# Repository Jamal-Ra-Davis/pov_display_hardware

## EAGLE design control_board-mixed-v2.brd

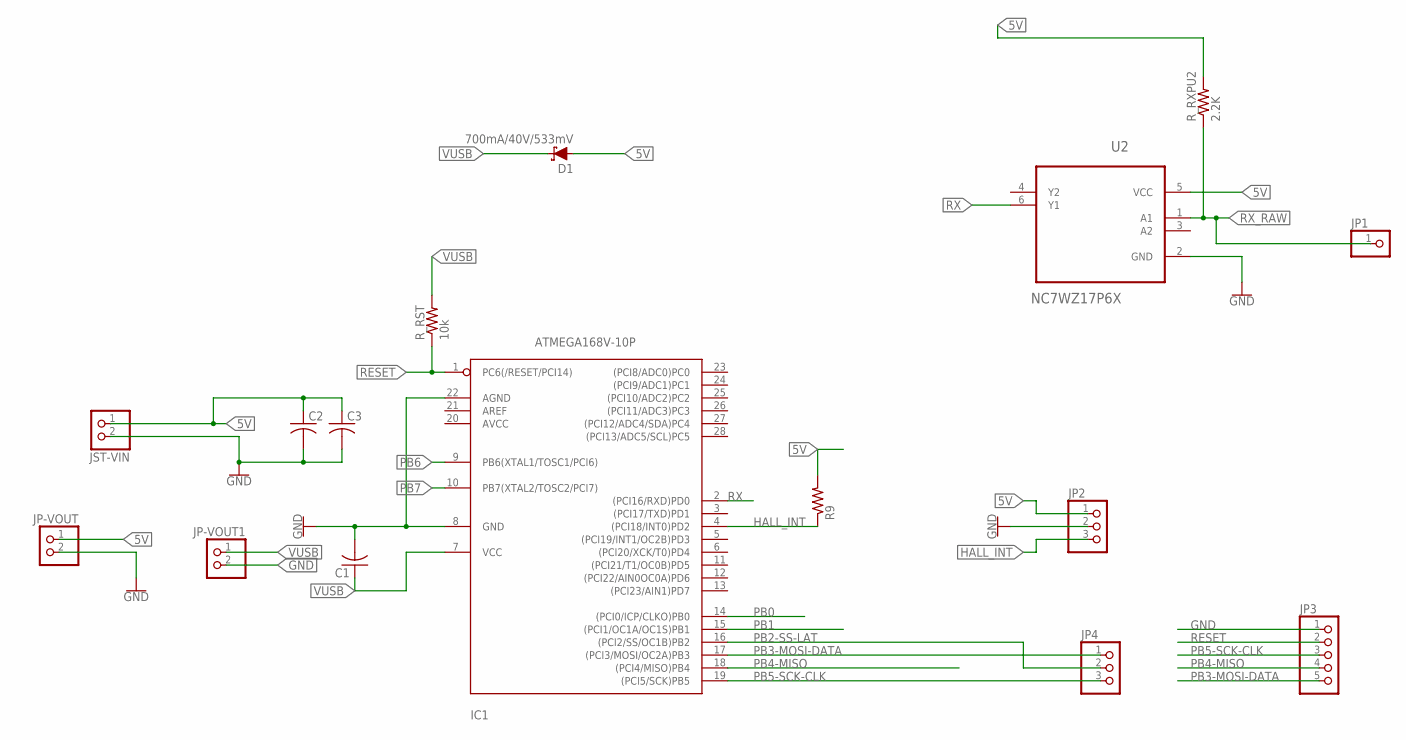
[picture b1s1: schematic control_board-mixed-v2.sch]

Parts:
C1: C-US025-030X050; C025-030X050
C2, C3: C-US025-060X050; C025-060X050
D1: 700mA/40V/533mV; SOT23-3
IC1: ATMEGA168V-10P; DIL28-3
JP1: PINHD-1X1; 1X01
JP2, JP4: PINHD-1X3; 1X03
JP3: PINHD-1X5; 1X05
JP-VOUT, JP-VOUT1: PINHD-1X2; 1X02
JST-VIN: JST_2PIN-THM-RA; JST-PH-2-THM-RA
R9: R-US_0207/7; 0207/7
R_RST: 10k; R0603
R_RXPU2: 2.2K; R0603
U2: NC7WZ17P6X; SOT65P210X110-6N

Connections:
5V: C2.1, C3.1, D1.1 (A), JP2.1, JP-VOUT.1, JST-VIN.1 (2), R9.2, R_RXPU2.2, U2.5 (VCC)
GND: C1.2, C2.2, C3.2, IC1.8 (GND), IC1.22 (AGND), JP2.2, JP3.1, JP-VOUT.2, JP-VOUT1.2, JST-VIN.2 (1), U2.2 (GND)
HALL_INT: IC1.4 ((PCI18/INT0)PD2), JP2.3, R9.1
PB0: IC1.14 ((PCI0/ICP/CLKO)PB0)
PB1: IC1.15 ((PCI1/OC1A/OC1S)PB1)
PB2-SS-LAT: IC1.16 ((PCI2/SS/OC1B)PB2), JP4.2
PB3-MOSI-DATA: IC1.17 ((PCI3/MOSI/OC2A)PB3), JP3.5, JP4.1
PB4-MISO: IC1.18 ((PCI4/MISO)PB4), JP3.4
PB5-SCK-CLK: IC1.19 ((PCI5/SCK)PB5), JP3.3, JP4.3
PB6: IC1.9 (PB6(XTAL1/TOSC1/PCI6))
PB7: IC1.10 (PB7(XTAL2/TOSC2/PCI7))
RESET: IC1.1 (PC6(/RESET/PCI14)), JP3.2, R_RST.1
RX: IC1.2 ((PCI16/RXD)PD0), U2.6 (Y1)
RX_RAW: JP1.1, R_RXPU2.1, U2.1 (A1)
VUSB: C1.1, D1.3 (C), IC1.7 (VCC), JP-VOUT1.1, R_RST.2

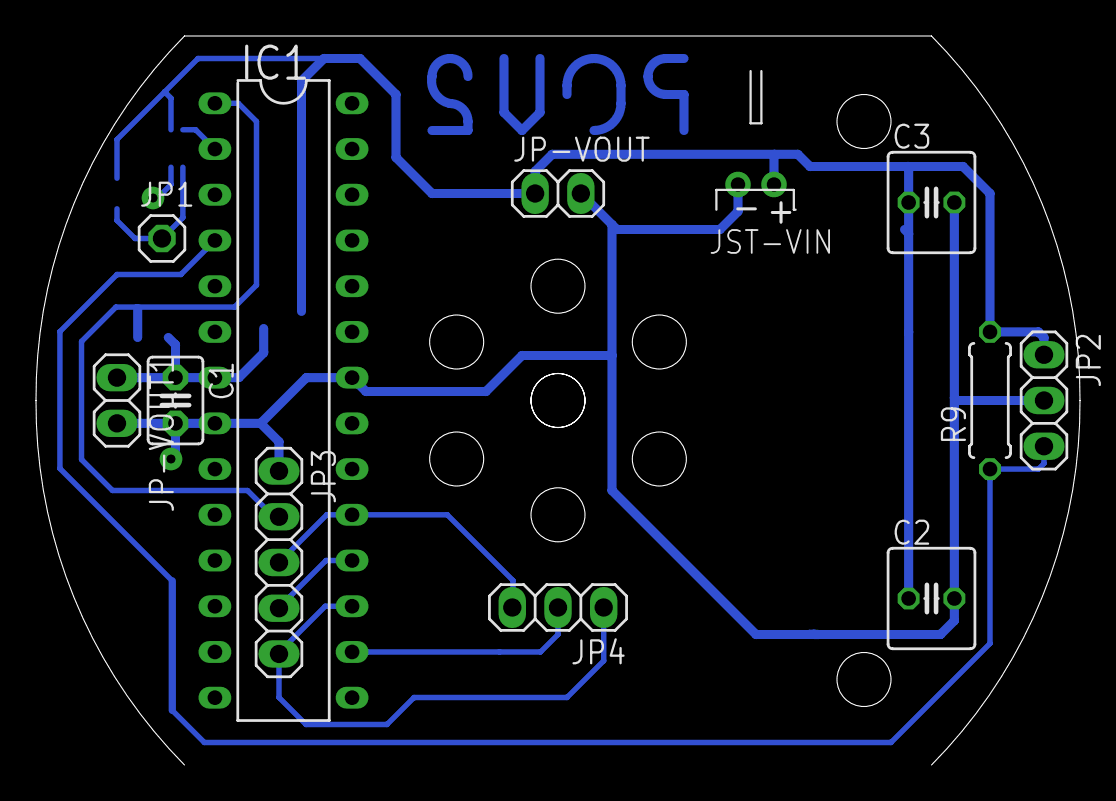
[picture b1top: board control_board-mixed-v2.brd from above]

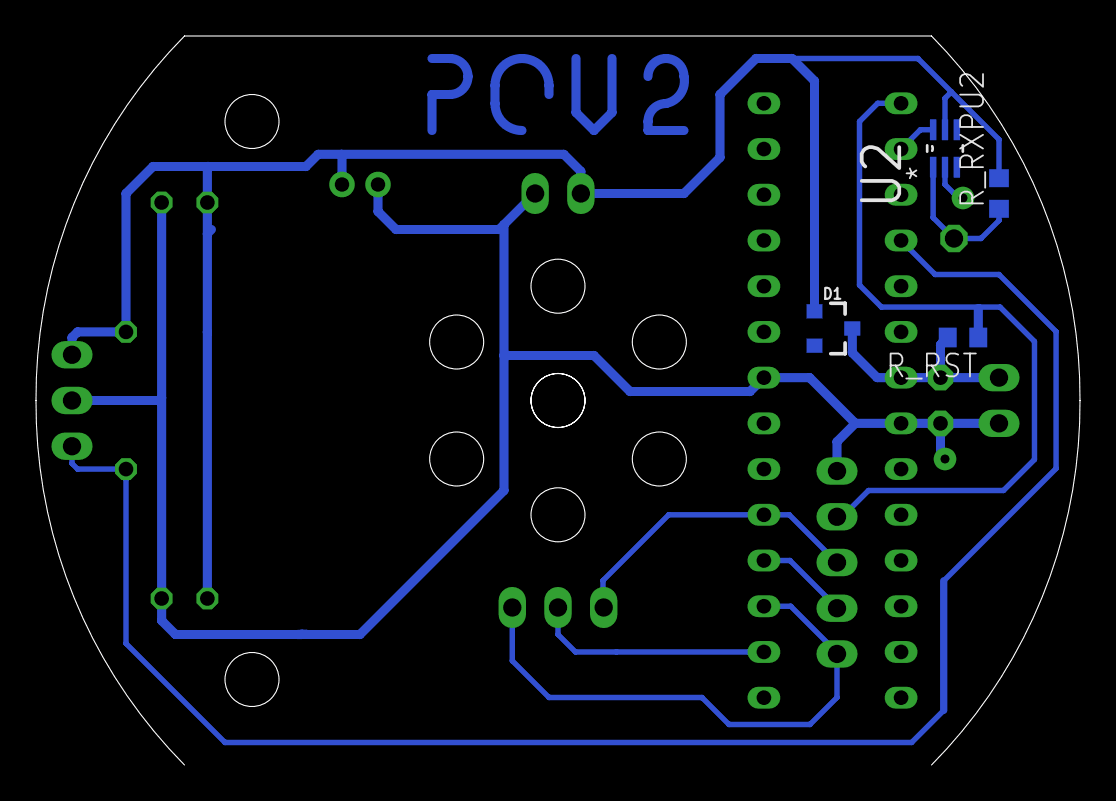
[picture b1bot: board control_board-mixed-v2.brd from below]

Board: 2 copper layers, 58.0 x 40.5 mm, 16 parts (4 on the bottom side), 11 nets.

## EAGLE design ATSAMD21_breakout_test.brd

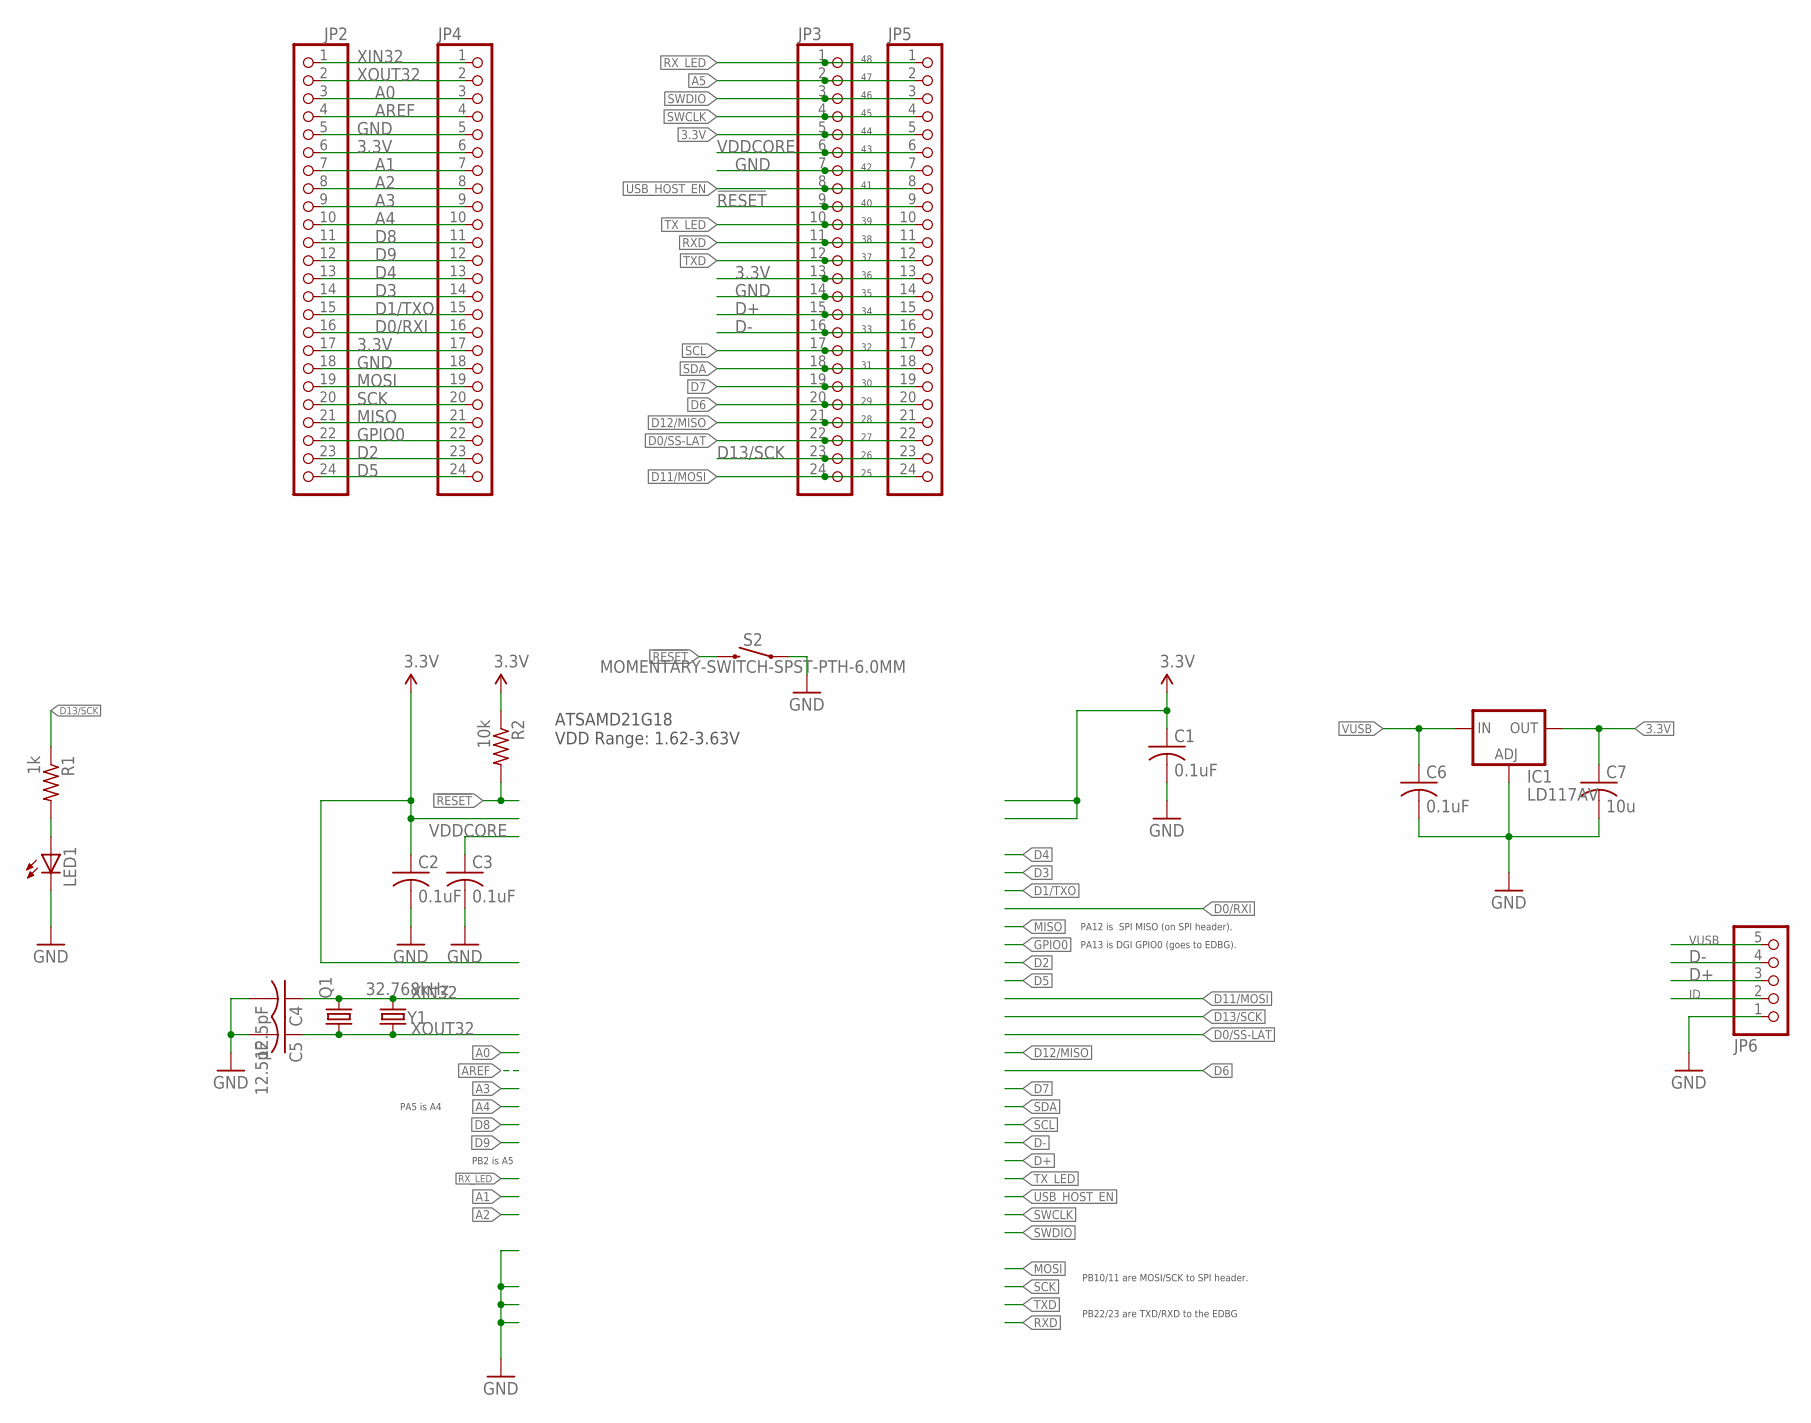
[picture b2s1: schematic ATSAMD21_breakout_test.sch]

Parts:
C1, C2, C3, C6: 0.1uF; C025-024X044
C4, C5: 12.5pF; C025-024X044
C7: 10u; C025-024X044
IC1: LD117AV; TO220L1
JP2, JP3, JP4, JP5: PINHD-1X24; 1X24
JP6: PINHD-1X5; 1X05
LED1: LED3MM
Q1: CRYSTALTC26V; TC26V
R1: 1k; 0204/7
R2: 10k; 0204/7
S2: MOMENTARY-SWITCH-SPST-PTH-6.0MM; TACTILE_SWITCH_PTH_6.0MM
Y1: 32.768kHz; CRYSTAL-SMD-3.2X1.5MM

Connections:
3.3V: C1.1, C2.1, C7.1, IC1.2 (OUT), JP2.6, JP2.17, JP3.5, JP3.13, JP4.6, JP4.17, JP5.5, JP5.13, R2.1
!RESET: JP3.9, JP5.9, R2.2, S2.3 (2)
A0: JP2.3, JP4.3
A1: JP2.7, JP4.7
A2: JP2.8, JP4.8
A3: JP2.9, JP4.9
A4: JP2.10, JP4.10
A5: JP3.2, JP5.2
AREF: JP2.4, JP4.4
D0/RXI: JP2.16, JP4.16
D0/SS-LAT: JP3.22, JP5.22
D1/TXO: JP2.15, JP4.15
D2: JP2.23, JP4.23
D3: JP2.14, JP4.14
D4: JP2.13, JP4.13
D5: JP2.24, JP4.24
D6: JP3.20, JP5.20
D7: JP3.19, JP5.19
D8: JP2.11, JP4.11
D9: JP2.12, JP4.12
D11/MOSI: JP3.24, JP5.24
D12/MISO: JP3.21, JP5.21
D13/SCK: JP3.23, JP5.23, R1.1
D+: JP3.15, JP5.15, JP6.3
D-: JP3.16, JP5.16, JP6.4
GND: C1.2, C2.2, C3.2, C4.2, C5.2, C6.2, C7.2, IC1.1 (ADJ), JP2.5, JP2.18, JP3.7, JP3.14, JP4.5, JP4.18, JP5.7, JP5.14, JP6.1, LED1.K (C), S2.1
GPIO0: JP2.22, JP4.22
ID: JP6.2
MISO: JP2.21, JP4.21
MOSI: JP2.19, JP4.19
unnamed: LED1.A, R1.2
RXD: JP3.11, JP5.11
RX_LED: JP3.1, JP5.1
SCK: JP2.20, JP4.20
SCL: JP3.17, JP5.17
SDA: JP3.18, JP5.18
SWCLK: JP3.4, JP5.4
SWDIO: JP3.3, JP5.3
TXD: JP3.12, JP5.12
TX_LED: JP3.10, JP5.10
USB_HOST_EN: JP3.8, JP5.8
VDDCORE: C3.1, JP3.6, JP5.6
VUSB: C6.1, IC1.3 (IN), JP6.5
XIN32: C4.1, JP2.1, JP4.1, Q1.2, Y1.P$2 (2)
XOUT32: C5.1, JP2.2, JP4.2, Q1.1, Y1.P$1 (1)

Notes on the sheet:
PB22/23 are TXD/RXD to the EDBG
PB10/11 are MOSI/SCK to SPI header.
PA12 is SPI MISO (on SPI header).
PA13 is DGI GPIO0 (goes to EDBG).
PA5 is A4
PB2 is A5
ATSAMD21G18 VDD Range: 1.62-3.63V

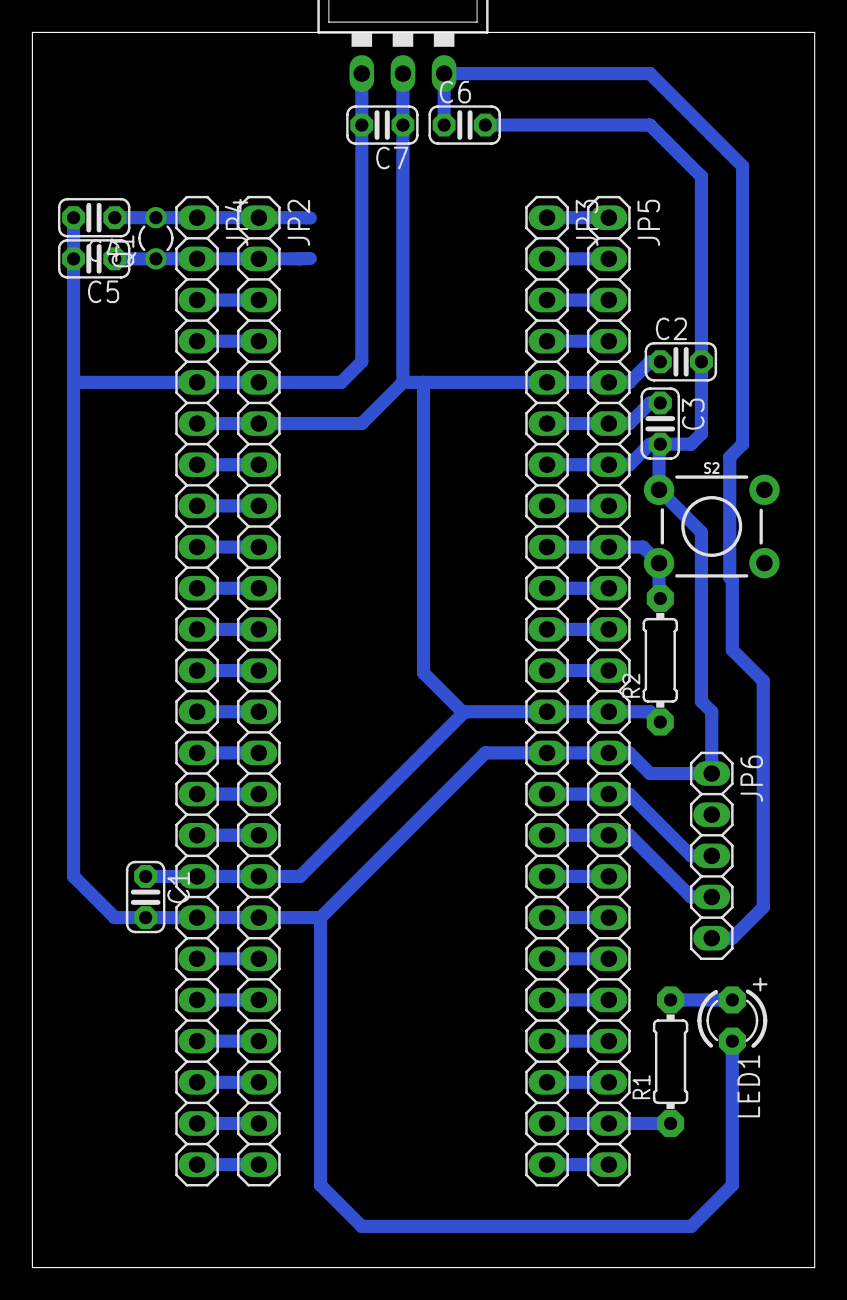
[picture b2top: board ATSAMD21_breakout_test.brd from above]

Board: 2 copper layers, 48.3 x 76.2 mm, 19 parts (1 on the bottom side), 44 nets.

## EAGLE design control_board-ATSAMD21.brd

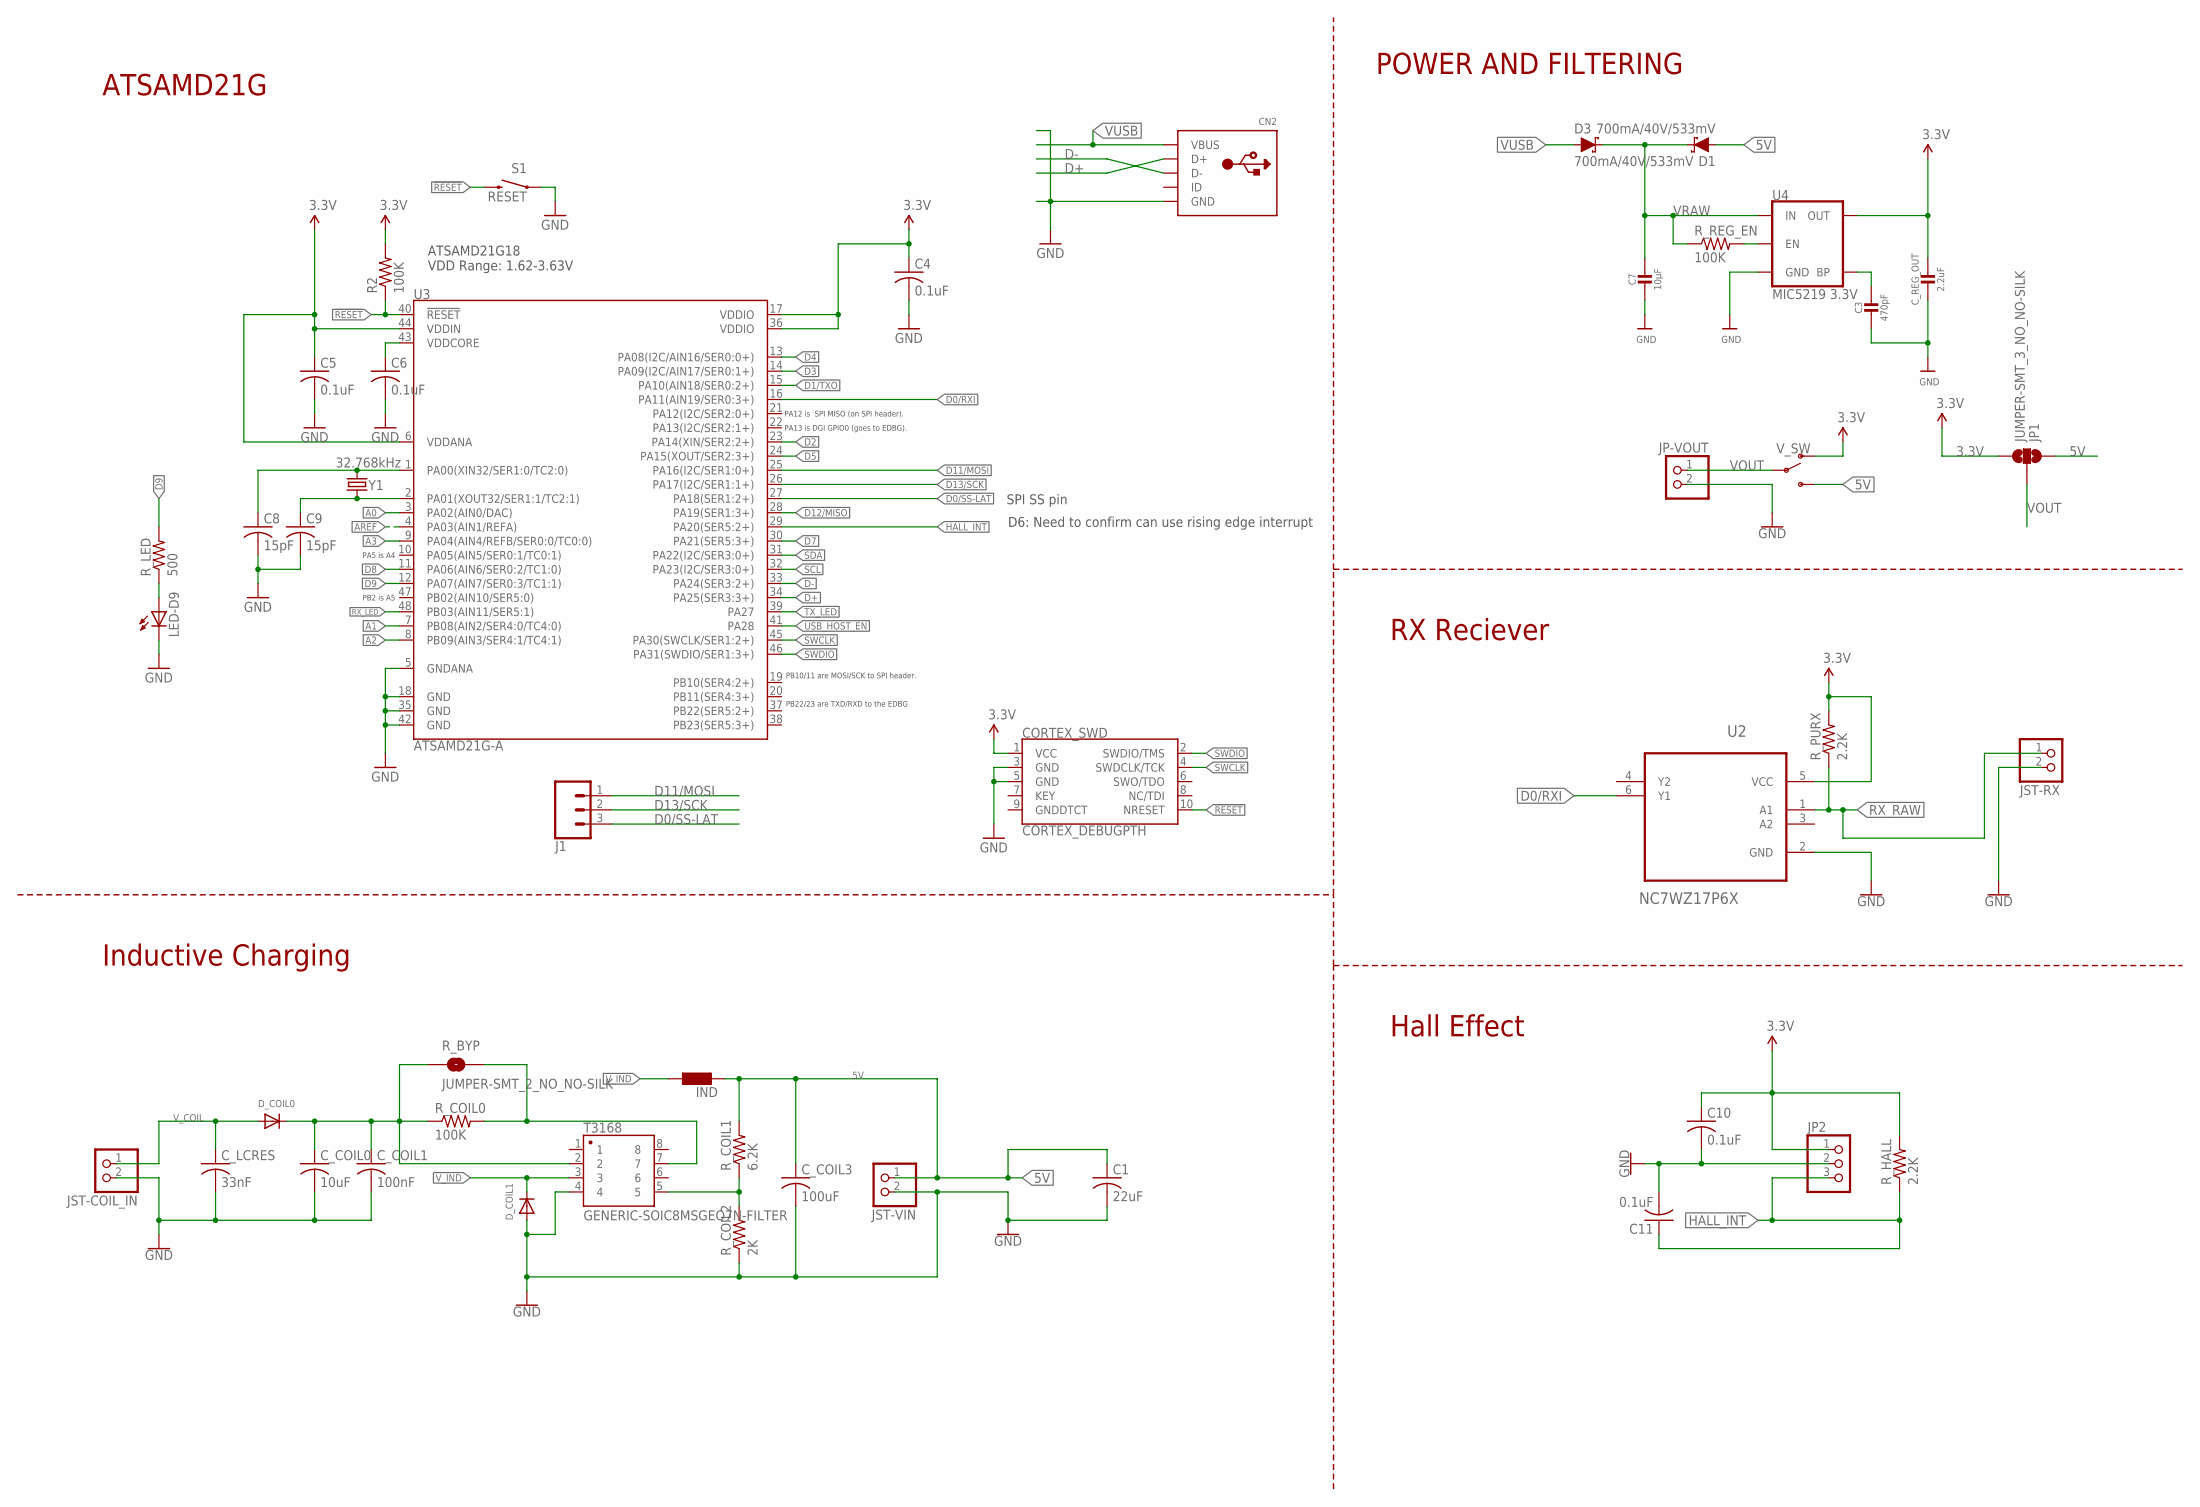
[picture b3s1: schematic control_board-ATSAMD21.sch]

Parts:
C1: 22uF; C1206
C3: 470pF; 0603-NO
C4, C5, C6, C10, C11: 0.1uF; C0603
C7: 10µF; 0805-NO
C8, C9: 15pF; C0603
CN2: USBTHM; USB-MINIB-THM
CORTEX_SWD: CORTEX_DEBUGPTH; 2X5-PTH-1.27MM
C_COIL0: 10uF; C1206
C_COIL1: 100nF; C1206
C_COIL3: 100uF; C1206
C_LCRES: 33nF; C1206
C_REG_OUT: 2.2uF; 0805-NO
D1, D3: 700mA/40V/533mV; SOT23-3
D_COIL0: DIODESMA; SMADIODE
D_COIL1: DIODE_SOD-123FL; SOD-123FL
IND: LL3230M; L3230M
J1: CONN_031X03_NO_SILK; 1X03_NO_SILK
JP1: JUMPER-SMT_3_NO_NO-SILK; SMT-JUMPER_3_NO_NO-SILK
JP2: PINHD-1X3; 1X03
JP-VOUT: PINHD-1X2; 1X02
JST-COIL_IN: JST_2PIN-THM-RA; JST-PH-2-THM-RA
JST-RX: JST_2PIN-THM-RA; JST-PH-2-THM-RA
JST-VIN: JST_2PIN-THM-RA; JST-PH-2-THM-RA
LED-D9: LEDCHIPLED_0603; CHIPLED_0603
R2: 100K; 0603-RES
R_BYP: JUMPER-SMT_2_NO_NO-SILK; SMT-JUMPER_2_NO_NO-SILK
R_COIL0: 100K; R0603
R_COIL1: 6.2K; R0603
R_COIL2: 2K; R0603
R_HALL: 2.2K; R0805
R_LED: 500; R0603
R_PURX: 2.2K; R0603
R_REG_EN: 100K; R0603
S1: RESET; TACTILE_SWITCH_SMD_4.6X2.8MM
T3168: GENERIC-SOIC8MSGEQ7N-FILTER; SO08
U2: NC7WZ17P6X; SOT65P210X110-6N
U3: ATSAMD21G-A; TQFP-48
U4: MIC5219 3.3V; SOT23-5
V_SW: SWITCH-SPDT-SMD-RIGHT-ANGLE; SWITCH_SPST_SMD_A
Y1: 32.768kHz; CRYSTAL-SMD-3.2X1.5MM

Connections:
3.3V: C4.1, C5.1, C10.1, CORTEX_SWD.1 (VCC), C_REG_OUT.1, JP1.3, JP2.1, R2.2, R_HALL.2, R_PURX.2, U2.5 (VCC), U3.6 (VDDANA), U3.17 (VDDIO), U3.36 (VDDIO), U3.44 (VDDIN), U4.5 (OUT), V_SW.1 (O)
5V: C1.1, C_COIL3.1, D1.1 (A), IND.2, JP1.1, JST-VIN.1 (2), R_COIL1.2, V_SW.3 (S)
!RESET: CORTEX_SWD.10 (NRESET), R2.1, S1.3 (2), S1.4 (2), U3.40 (!RESET!)
A0: U3.3 (PA02(AIN0/DAC))
A1: U3.7 (PB08(AIN2/SER4:0/TC4:0))
A2: U3.8 (PB09(AIN3/SER4:1/TC4:1))
A3: U3.9 (PA04(AIN4/REFB/SER0:0/TC0:0))
AREF: U3.4 (PA03(AIN1/REFA))
D0/RXI: U2.6 (Y1), U3.16 (PA11(AIN19/SER0:3+))
D0/SS-LAT: J1.3, U3.27 (PA18(SER1:2+))
D1/TXO: U3.15 (PA10(AIN18/SER0:2+))
D2: U3.23 (PA14(XIN/SER2:2+))
D3: U3.14 (PA09(I2C/AIN17/SER0:1+))
D4: U3.13 (PA08(I2C/AIN16/SER0:0+))
D5: U3.24 (PA15(XOUT/SER2:3+))
D7: U3.30 (PA21(SER5:3+))
D8: U3.11 (PA06(AIN6/SER0:2/TC1:0))
D9: R_LED.2, U3.12 (PA07(AIN7/SER0:3/TC1:1))
D11/MOSI: J1.1, U3.25 (PA16(I2C/SER1:0+))
D12/MISO: U3.28 (PA19(SER1:3+))
D13/SCK: J1.2, U3.26 (PA17(I2C/SER1:1+))
D+: CN2.D+, U3.34 (PA25(SER3:3+))
D-: CN2.D-, U3.33 (PA24(SER3:2+))
GND: C1.2, C3.2, C4.2, C5.2, C6.2, C7.2, C8.2, C9.2, C10.2, C11.2, CN2.GND, CORTEX_SWD.3 (GND), CORTEX_SWD.5 (GND), C_COIL0.2, C_COIL1.2, C_COIL3.2, C_LCRES.2, C_REG_OUT.2, D_COIL1.A, JP2.2, JP-VOUT.2, JST-COIL_IN.2 (1), JST-RX.2 (1), JST-VIN.2 (1), LED-D9.C, R_COIL2.1, S1.1, S1.2 (1), T3168.4, U2.2 (GND), U3.5 (GNDANA), U3.18 (GND), U3.35 (GND), U3.42 (GND), U4.2 (GND)
HALL_INT: C11.1, JP2.3, R_HALL.1, U3.29 (PA20(SER5:2+))
unnamed: C_COIL0.1, C_COIL1.1, D_COIL0.C, R_BYP.1, R_COIL0.1, T3168.2
unnamed: C8.1, U3.1 (PA00(XIN32/SER1:0/TC2:0)), Y1.P$2 (2)
unnamed: R_COIL1.1, R_COIL2.2, T3168.5
unnamed: C9.1, U3.2 (PA01(XOUT32/SER1:1/TC2:1)), Y1.P$1 (1)
unnamed: R_REG_EN.2, U4.3 (EN)
unnamed: C3.1, U4.4 (BP)
unnamed: R_BYP.2, R_COIL0.2, T3168.7
unnamed: LED-D9.A, R_LED.1
RX_LED: U3.48 (PB03(AIN11/SER5:1))
RX_RAW: JST-RX.1 (2), R_PURX.1, U2.1 (A1)
SCL: U3.32 (PA23(I2C/SER3:0+))
SDA: U3.31 (PA22(I2C/SER3:0+))
SWCLK: CORTEX_SWD.4 (SWDCLK/TCK), U3.45 (PA30(SWCLK/SER1:2+))
SWDIO: CORTEX_SWD.2 (SWDIO/TMS), U3.46 (PA31(SWDIO/SER1:3+))
TX_LED: U3.39 (PA27)
USB_HOST_EN: U3.41 (PA28)
VDDCORE: C6.1, U3.43 (VDDCORE)
VOUT: JP1.2, JP-VOUT.1, V_SW.2
VRAW: C7.1, D1.3 (C), D3.3 (C), R_REG_EN.1, U4.1 (IN)
VUSB: CN2.VBUS, D3.1 (A)
V_COIL: C_LCRES.1, D_COIL0.A, JST-COIL_IN.1 (2)
V_IND: D_COIL1.C, IND.1, T3168.3

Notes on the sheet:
POWER AND FILTERING
PB22/23 are TXD/RXD to the EDBG
PB10/11 are MOSI/SCK to SPI header.
PA12 is SPI MISO (on SPI header).
PA13 is DGI GPIO0 (goes to EDBG).
PA5 is A4
PB2 is A5
ATSAMD21G
ATSAMD21G18 VDD Range: 1.62-3.63V
SPI SS pin
D6: Need to confirm can use rising edge interrupt
Inductive Charging
RX Reciever
Hall Effect

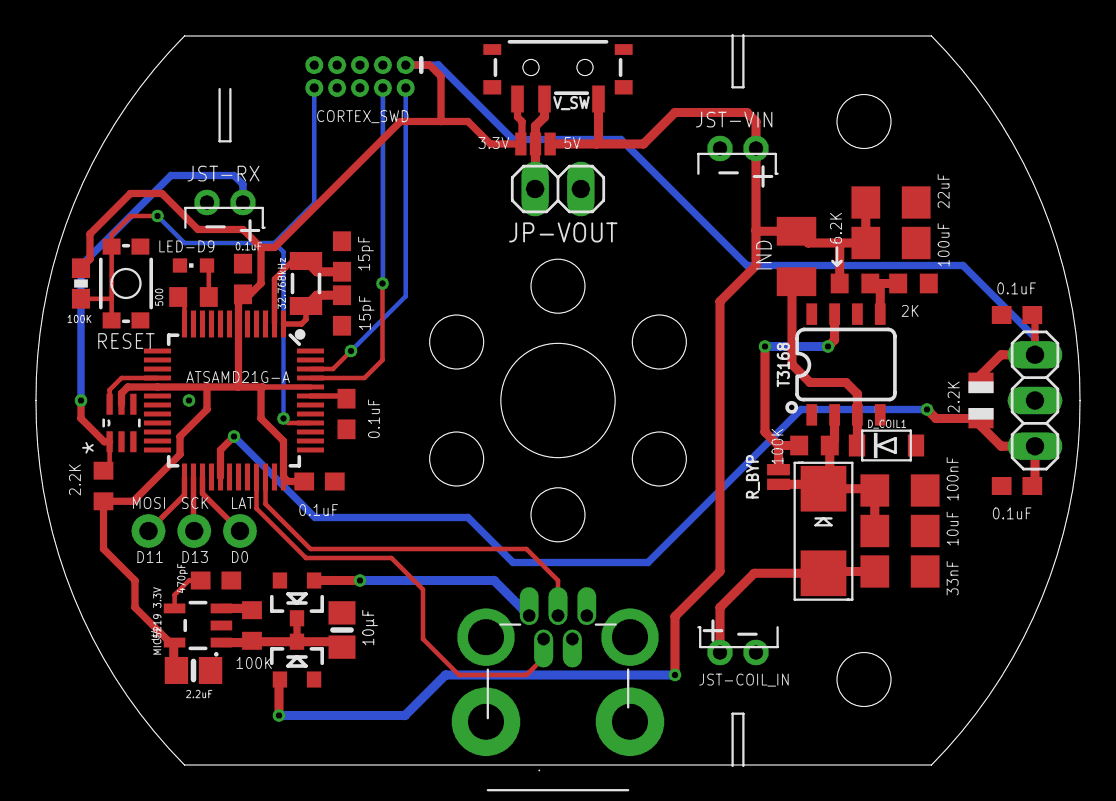
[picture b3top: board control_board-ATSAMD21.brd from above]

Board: 2 copper layers, 58.0 x 40.5 mm, 46 parts (0 on the bottom side), 29 nets.

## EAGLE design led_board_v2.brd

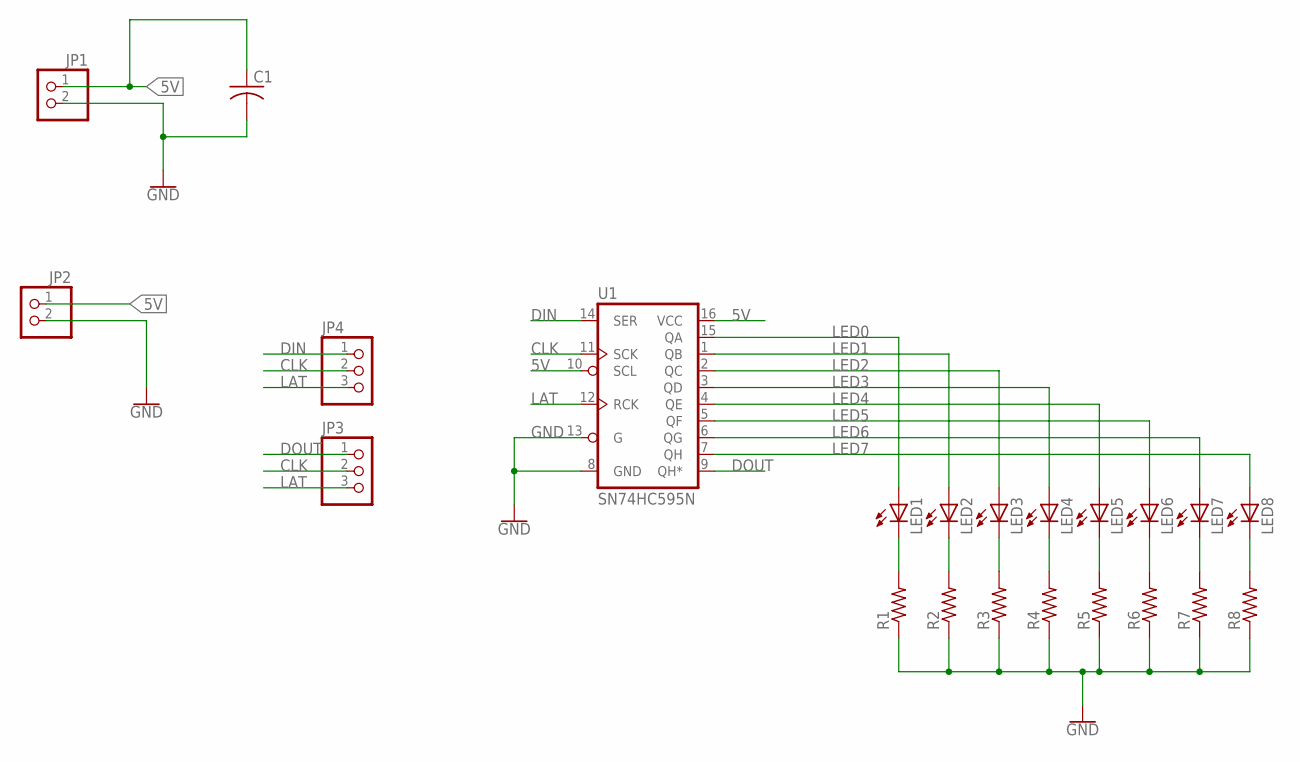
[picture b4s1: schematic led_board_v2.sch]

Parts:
C1: C-US025-030X050; C025-030X050
JP1, JP2: PINHD-1X2; 1X02
JP3, JP4: PINHD-1X3; 1X03
LED1, LED2, LED3, LED4, LED5, LED6, LED7, LED8: LED3MM
R1, R2, R3, R4, R5, R6, R7, R8: R-US_0207/7; 0207/7
U1: SN74HC595N; DIP16

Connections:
5V: C1.1, JP1.1, JP2.1, U1.10 (SCL), U1.16 (VCC)
CLK: JP3.2, JP4.2, U1.11 (SCK)
DIN: JP4.1, U1.14 (SER)
DOUT: JP3.1, U1.9 (QH*)
GND: C1.2, JP1.2, JP2.2, R1.1, R2.1, R3.1, R4.1, R5.1, R6.1, R7.1, R8.1, U1.8 (GND), U1.13 (G)
LAT: JP3.3, JP4.3, U1.12 (RCK)
LED0: LED1.A, U1.15 (QA)
LED1: LED2.A, U1.1 (QB)
LED2: LED3.A, U1.2 (QC)
LED3: LED4.A, U1.3 (QD)
LED4: LED5.A, U1.4 (QE)
LED5: LED6.A, U1.5 (QF)
LED6: LED7.A, U1.6 (QG)
LED7: LED8.A, U1.7 (QH)
unnamed: LED1.K (C), R1.2
unnamed: LED2.K (C), R2.2
unnamed: LED3.K (C), R3.2
unnamed: LED4.K (C), R4.2
unnamed: LED5.K (C), R5.2
unnamed: LED6.K (C), R6.2
unnamed: LED7.K (C), R7.2
unnamed: LED8.K (C), R8.2

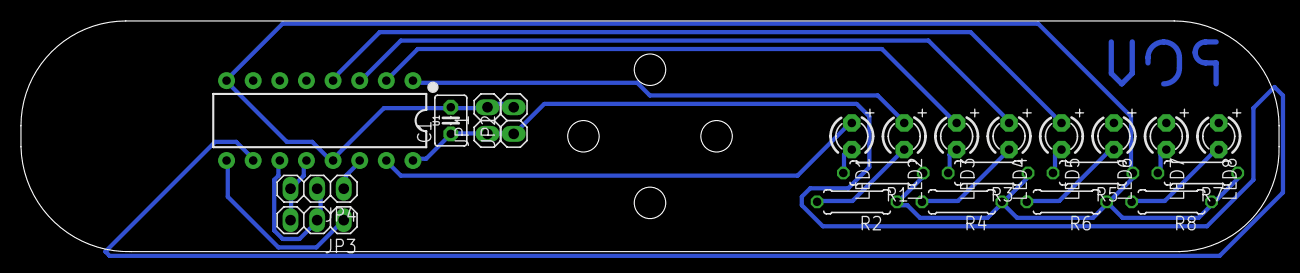
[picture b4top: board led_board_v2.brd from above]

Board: 2 copper layers, 120.0 x 22.0 mm, 22 parts (0 on the bottom side), 22 nets.

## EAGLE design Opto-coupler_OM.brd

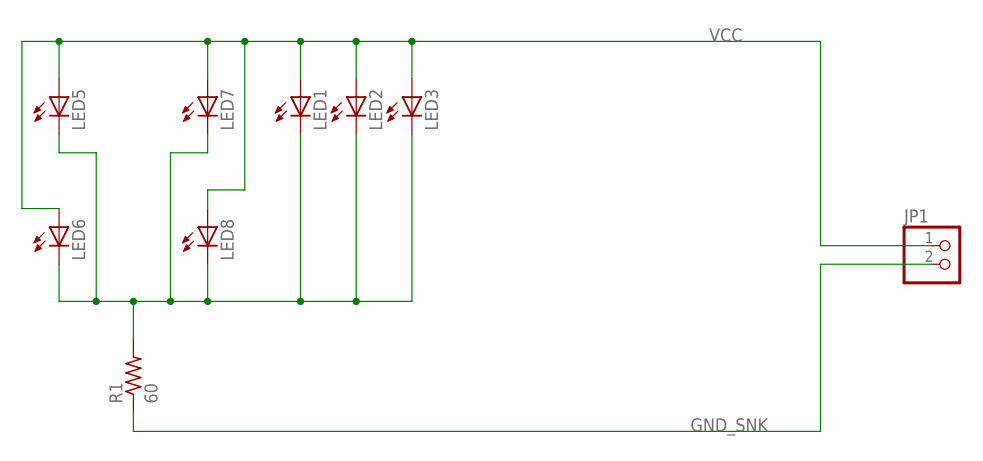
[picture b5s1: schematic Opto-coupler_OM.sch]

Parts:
JP1: PINHD-1X2; 1X02
LED1, LED2, LED3, LED5, LED6, LED7, LED8: LED3MM
R1: 60; 0204/7

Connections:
GND_SNK: JP1.2, R1.1
unnamed: LED1.K (C), LED2.K (C), LED3.K (C), LED5.K (C), LED6.K (C), LED7.K (C), LED8.K (C), R1.2
VCC: JP1.1, LED1.A, LED2.A, LED3.A, LED5.A, LED6.A, LED7.A, LED8.A

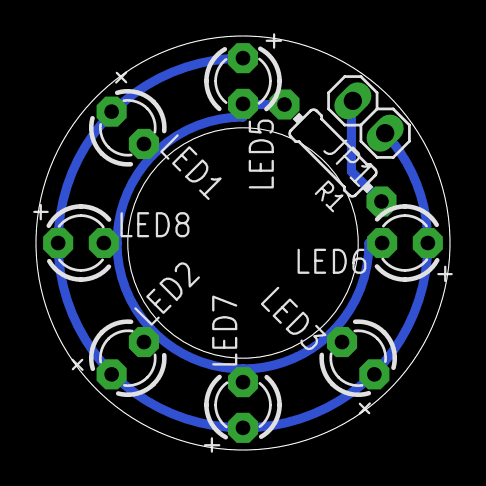
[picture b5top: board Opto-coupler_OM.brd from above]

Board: 2 copper layers, 23.0 x 23.0 mm, 9 parts (0 on the bottom side), 3 nets.

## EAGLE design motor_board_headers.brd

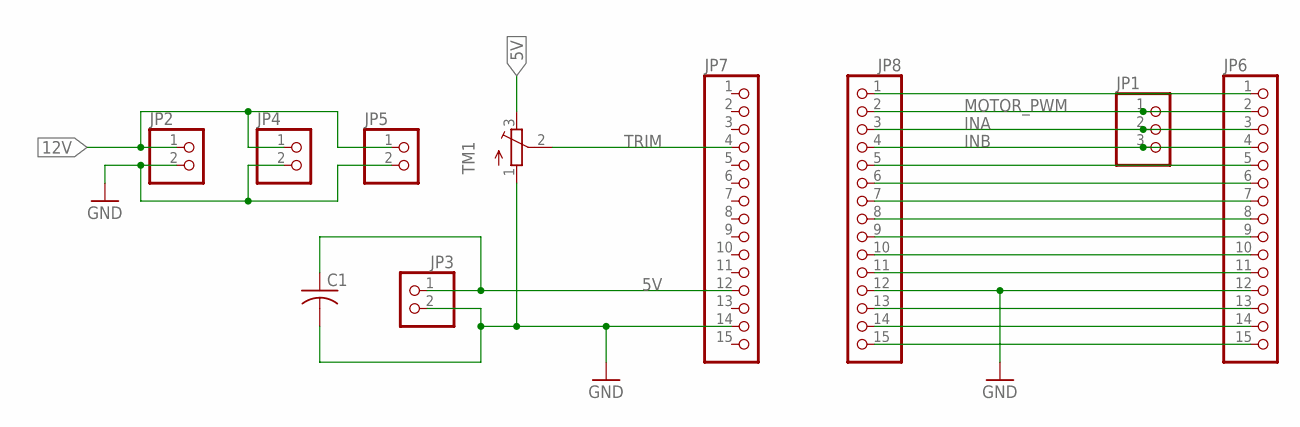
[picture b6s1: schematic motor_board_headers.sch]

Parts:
C1: C-US025-060X050; C025-060X050
JP1: PINHD-1X3; 1X03
JP2, JP3, JP4, JP5: PINHD-1X2; 1X02
JP6, JP7, JP8: PINHD-1X15; 1X15
TM1: TRIMPOT3386; TRIM-3386

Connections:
5V: C1.1, JP3.1, JP7.12, TM1.3 (E)
12V: JP2.1, JP4.1, JP5.1
GND: C1.2, JP2.2, JP3.2, JP4.2, JP5.2, JP6.12, JP7.14, JP8.12, TM1.1 (A)
INA: JP1.2, JP6.3, JP8.3
INB: JP1.3, JP6.4, JP8.4
MOTOR_PWM: JP1.1, JP6.2, JP8.2
unnamed: JP6.1, JP8.1
unnamed: JP6.5, JP8.5
unnamed: JP6.6, JP8.6
unnamed: JP6.7, JP8.7
unnamed: JP6.8, JP8.8
unnamed: JP6.9, JP8.9
unnamed: JP6.10, JP8.10
unnamed: JP6.11, JP8.11
unnamed: JP6.13, JP8.13
unnamed: JP6.14, JP8.14
unnamed: JP6.15, JP8.15
TRIM: JP7.4, TM1.2 (S)

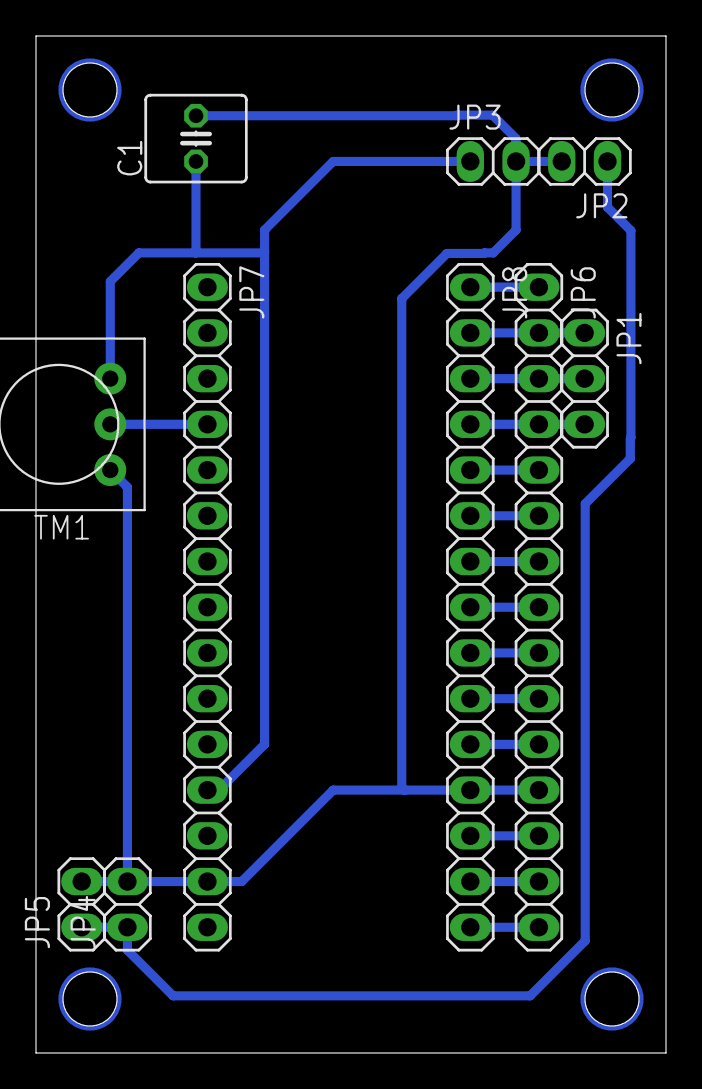
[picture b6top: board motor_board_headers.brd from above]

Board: 2 copper layers, 35.0 x 56.5 mm, 10 parts (0 on the bottom side), 18 nets.

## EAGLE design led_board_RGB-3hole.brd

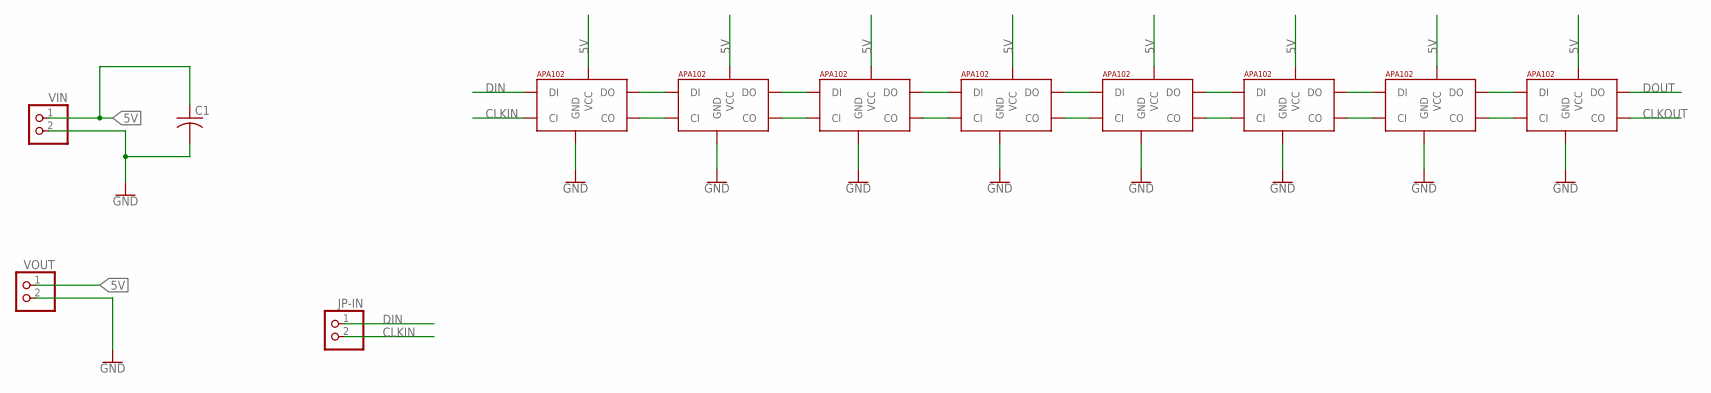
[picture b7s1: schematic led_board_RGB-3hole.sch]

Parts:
C1: C-US025-030X050; C025-030X050
ED4: APA1025050; APA102_5050
JP-IN: PINHD-1X2; 1X02
LED0, LED1, LED2, LED3, LED5, LED6, LED7: APA1025050; APA102_5050
VIN: PINHD-1X2; 1X02
VOUT: PINHD-1X2; 1X02

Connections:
5V: C1.1, ED4.1 (VCC), LED0.1 (VCC), LED1.1 (VCC), LED2.1 (VCC), LED3.1 (VCC), LED5.1 (VCC), LED6.1 (VCC), LED7.1 (VCC), VIN.1, VOUT.1
CLKIN: JP-IN.2, LED0.5 (CI)
CLKOUT: LED7.2 (CO)
DIN: JP-IN.1, LED0.4 (DI)
DOUT: LED7.3 (DO)
GND: C1.2, ED4.6 (GND), LED0.6 (GND), LED1.6 (GND), LED2.6 (GND), LED3.6 (GND), LED5.6 (GND), LED6.6 (GND), LED7.6 (GND), VIN.2, VOUT.2
unnamed: LED0.3 (DO), LED1.4 (DI)
unnamed: LED0.2 (CO), LED1.5 (CI)
unnamed: LED1.3 (DO), LED2.4 (DI)
unnamed: LED1.2 (CO), LED2.5 (CI)
unnamed: LED2.3 (DO), LED3.4 (DI)
unnamed: LED2.2 (CO), LED3.5 (CI)
unnamed: ED4.4 (DI), LED3.3 (DO)
unnamed: ED4.5 (CI), LED3.2 (CO)
unnamed: ED4.3 (DO), LED5.4 (DI)
unnamed: ED4.2 (CO), LED5.5 (CI)
unnamed: LED5.3 (DO), LED6.4 (DI)
unnamed: LED5.2 (CO), LED6.5 (CI)
unnamed: LED6.3 (DO), LED7.4 (DI)
unnamed: LED6.2 (CO), LED7.5 (CI)

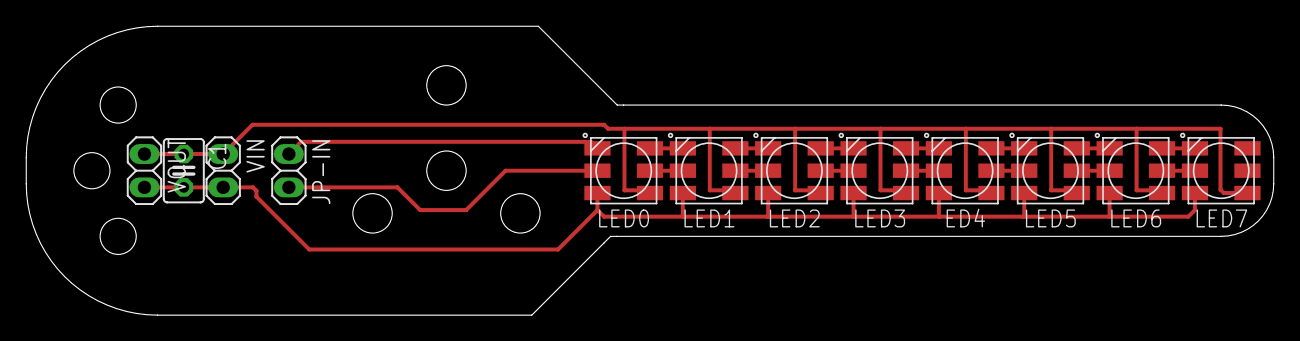
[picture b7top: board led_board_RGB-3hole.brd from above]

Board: 2 copper layers, 95.0 x 22.0 mm, 12 parts (0 on the bottom side), 18 nets.

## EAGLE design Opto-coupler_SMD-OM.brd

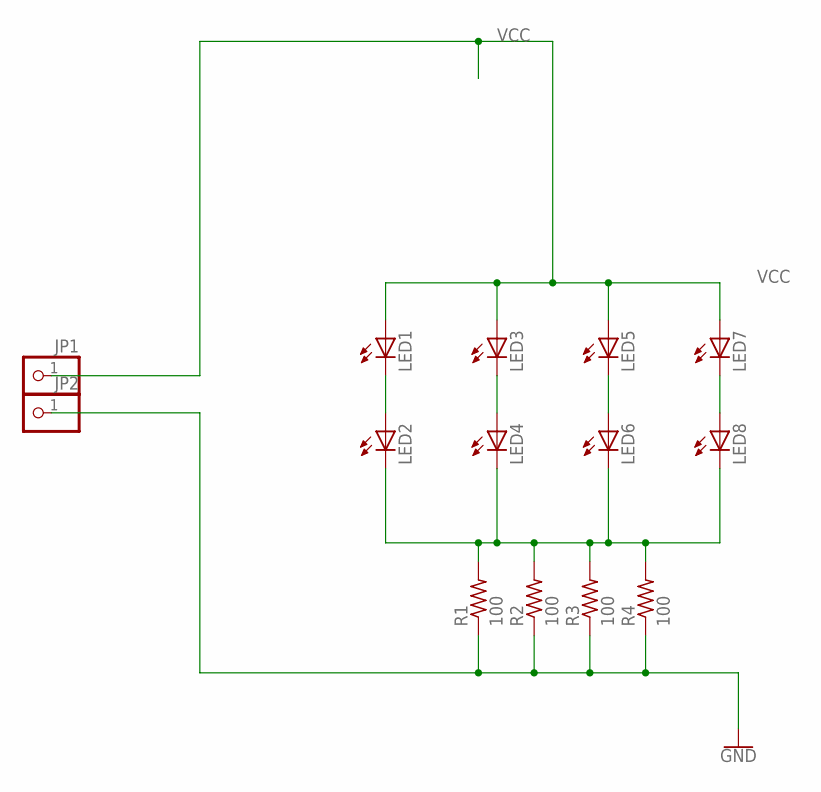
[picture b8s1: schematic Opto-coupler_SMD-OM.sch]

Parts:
JP1, JP2: PINHD-1X1; 1X01
LED1, LED2, LED3, LED4, LED5, LED6, LED7, LED8: LEDCHIPLED_0603; CHIPLED_0603
R1, R2, R3, R4: 100; R0603

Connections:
GND: JP2.1, R1.1, R2.1, R3.1, R4.1
unnamed: LED1.C, LED2.A
unnamed: LED2.C, LED4.C, LED6.C, LED8.C, R1.2, R2.2, R3.2, R4.2
unnamed: LED3.C, LED4.A
unnamed: LED5.C, LED6.A
unnamed: LED7.C, LED8.A
VCC: JP1.1, LED1.A, LED3.A, LED5.A, LED7.A

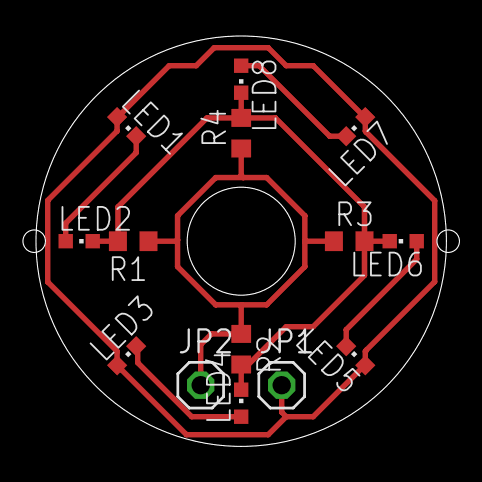
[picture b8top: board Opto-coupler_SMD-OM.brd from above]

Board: 2 copper layers, 22.8 x 22.8 mm, 14 parts (0 on the bottom side), 7 nets.

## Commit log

2019-05-25 Eagle hardware files for POV display as of 5/25/2019. Currently in stable state, with atsamd21 based control board with intrgrated inductive charging circuitrry (transplanted from adafruit boards), a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

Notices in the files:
parts and their libraries:
SparkFun-Switches: Licensing: Creative Commons ShareAlike 4.0 International - https://creativecommons.org/licenses/by-sa/4.0
microbuilder: This work is placed in the public domain, and may be freely used for commercial and non-commercial work with the following conditions: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
